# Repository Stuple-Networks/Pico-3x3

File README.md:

A DIY MacroPad using the Pi Pico with the Rp2040 Chip

Plan: Getting Merged into VIA Repo   
Currently: Planning on getting merged with QMK Firmware

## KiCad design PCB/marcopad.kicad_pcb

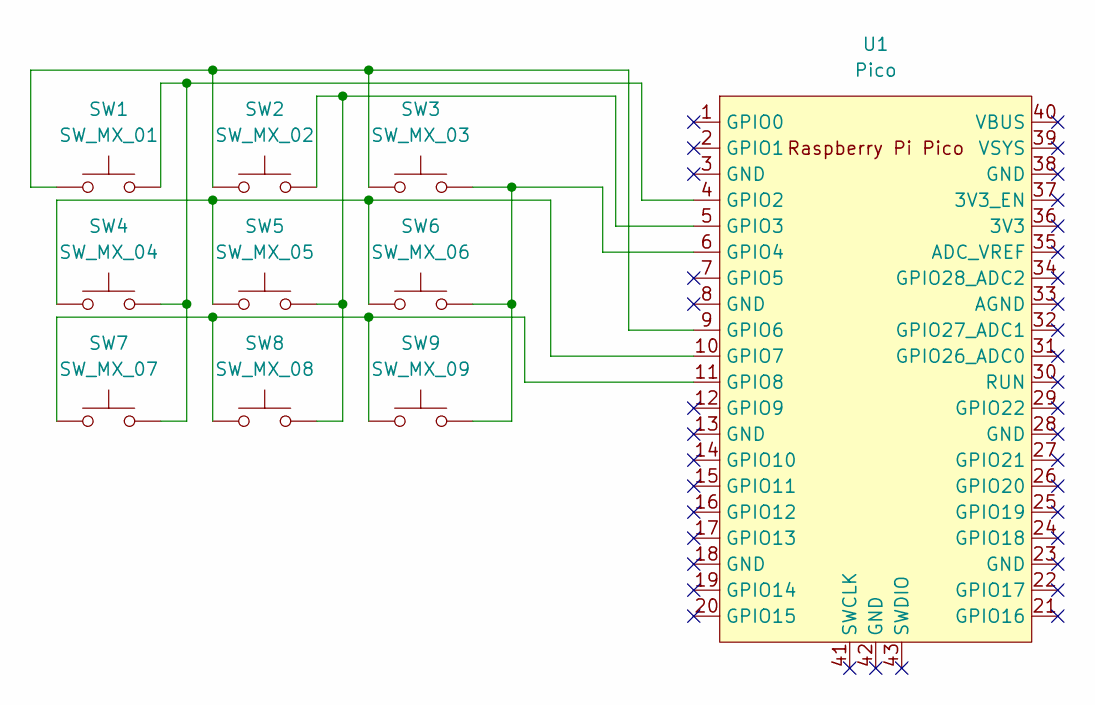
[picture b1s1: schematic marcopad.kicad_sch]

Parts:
SW1: SW_MX_01; MX100H
SW2: SW_MX_02; MX100H
SW3: SW_MX_03; MX100H
SW4: SW_MX_04; MX100H
SW5: SW_MX_05; MX100H
SW6: SW_MX_06; MX100H
SW7: SW_MX_07; MX100H
SW8: SW_MX_08; MX100H
SW9: SW_MX_09; MX100H
U1: Pico; RaspberryPi_Pico_Original_SMD_MountingHoles

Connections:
unnamed: SW1.2, SW4.2, SW7.2, U1.4 (GPIO2)
unnamed: SW2.2, SW5.2, SW8.2, U1.5 (GPIO3)
unnamed: SW3.2, SW6.2, SW9.2, U1.6 (GPIO4)
unnamed: SW1.1, SW2.1, SW3.1, U1.9 (GPIO6)
unnamed: SW4.1, SW5.1, SW6.1, U1.10 (GPIO7)
unnamed: SW7.1, SW8.1, SW9.1, U1.11 (GPIO8)

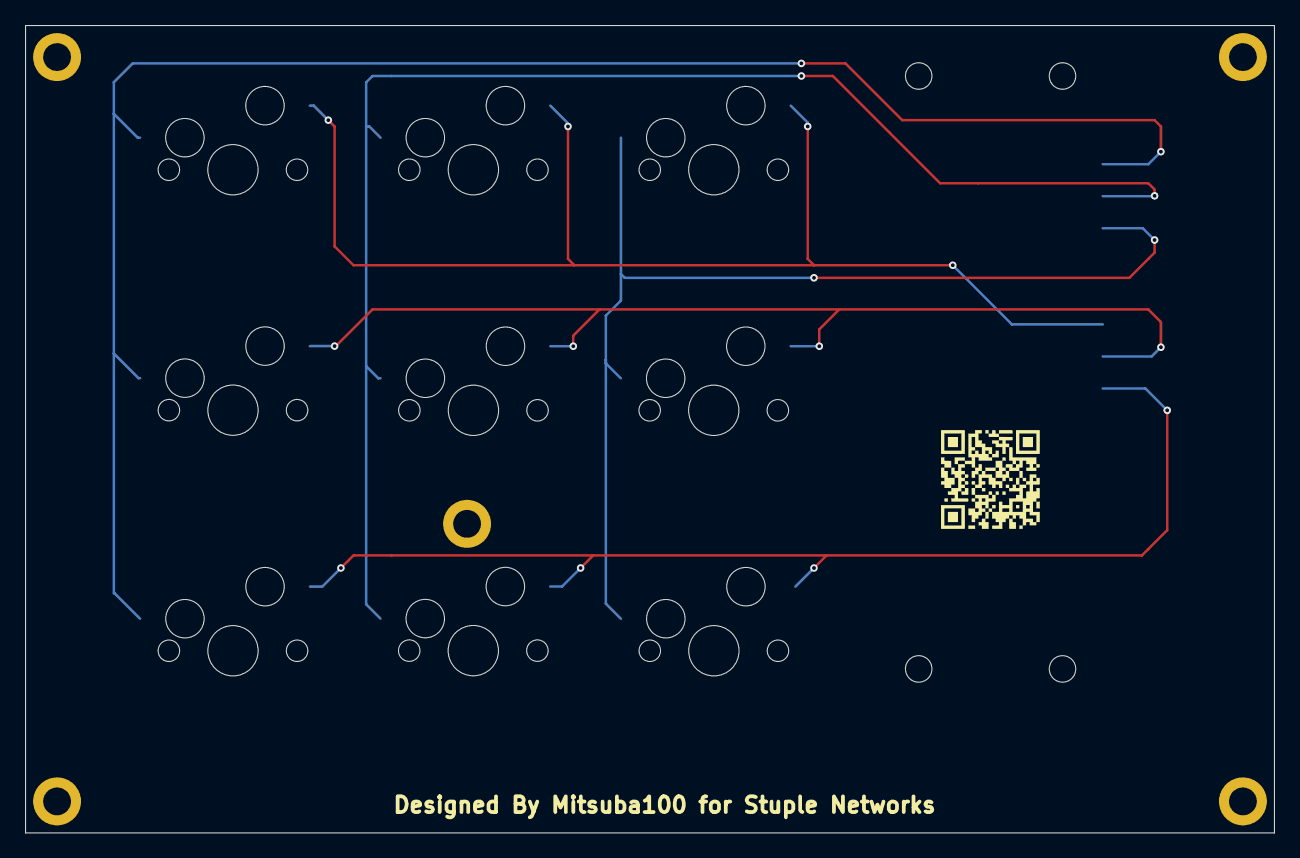
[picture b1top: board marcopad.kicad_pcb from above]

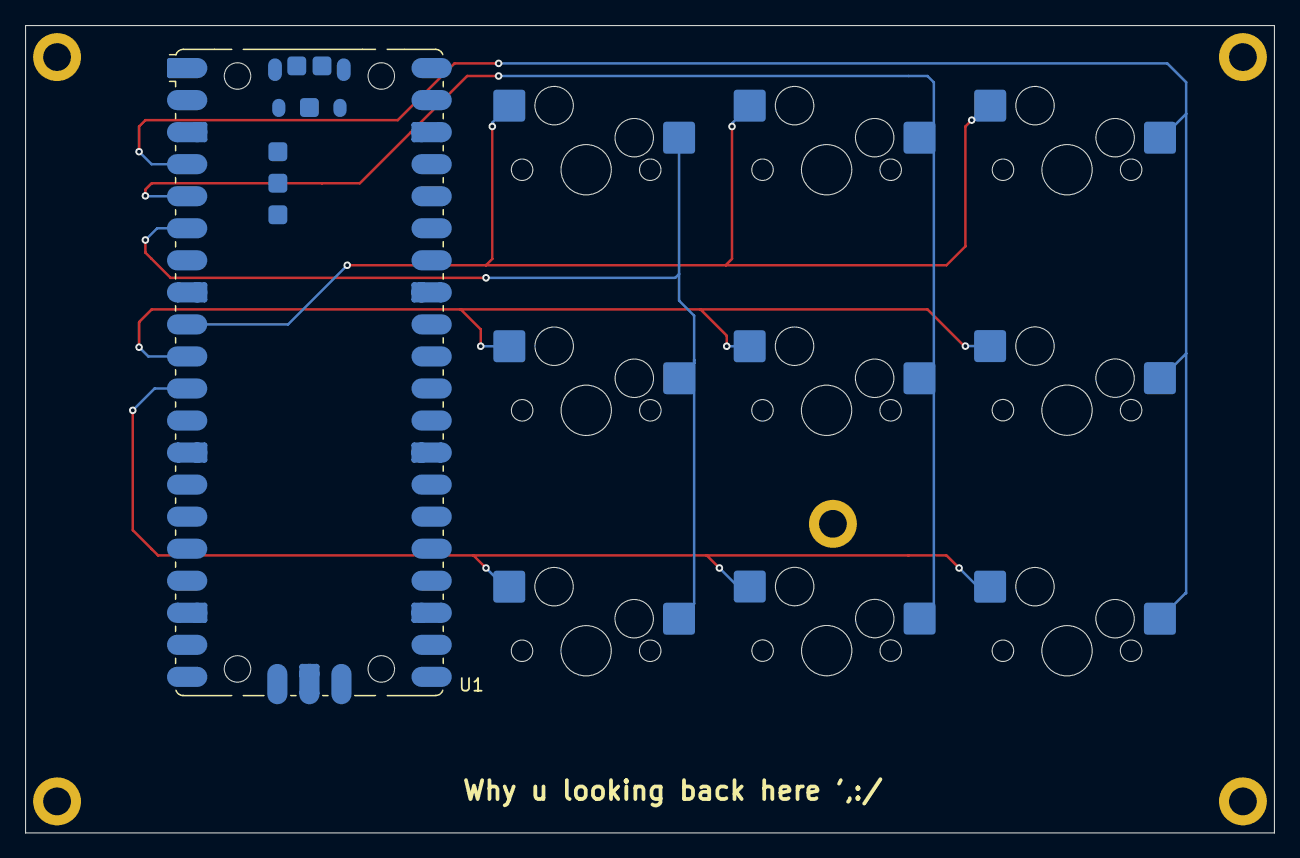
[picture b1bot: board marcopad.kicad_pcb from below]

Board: 2 copper layers, 99.0 x 64.0 mm, 10 parts (10 on the bottom side), 6 nets.

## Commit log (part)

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2026-01-20 Create LICENSE
2026-02-05 Add EXTRAKEY_ENABLE to rules.mk
